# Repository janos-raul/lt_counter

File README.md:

# longitudinal counter 
* [esp32](https://randomnerdtutorials.com/getting-started-with-esp32/) dev board
* [atmega1284p](https://www.aliexpress.com/item/1005007821134063.html?spm=a2g0o.productlist.main.11.9c24lJzhlJzhrd&algo_pvid=f090fad8-6947-47ad-9f22-427393e42094&algo_exp_id=f090fad8-6947-47ad-9f22-427393e42094-5&pdp_npi=4%40dis%21RON%2138.18%2138.18%21%21%2156.89%2156.89%21%402103846917361967912061487e2941%2112000042327493490%21sea%21RO%21187544673%21X&curPageLogUid=a42hYKpOFvhT&utparam-url=scene%3Asearch%7Cquery_from%3A)
* 20x4 [LCD display](https://www.tme.eu/ro/details/rc2004c-ygn-esx/afisaje-lcd-alfanumerice/raystar-optronics/)
* [JDY-41](https://www.aliexpress.com/item/1005003207184013.html?spm=a2g0o.productlist.main.1.15561p5u1p5ukG&algo_pvid=208953bd-97a7-4039-9dab-6f45cec27f1f&algo_exp_id=208953bd-97a7-4039-9dab-6f45cec27f1f-0&pdp_npi=4%40dis%21RON%218.14%218.14%21%21%211.65%211.65%21%402103890917361965765133329ed915%2112000024661701587%21sea%21RO%21187544673%21X&curPageLogUid=vka9Aeq0vKJ6&utparam-url=scene%3Asearch%7Cquery_from%3A) transparent serial port radio module for comunication between the avr and esp32
* [AHT15](https://www.aliexpress.com/item/1005002315840675.html?spm=a2g0o.productlist.main.5.32b8blGTblGTdS&algo_pvid=7e802fce-aae0-4a5e-818c-5492766aa2da&algo_exp_id=7e802fce-aae0-4a5e-818c-5492766aa2da-2&pdp_npi=4%40dis%21RON%219.87%218.69%21%21%212.00%211.76%21%40211b430817361963530388556eb844%2112000043098964036%21sea%21RO%210%21ABX&curPageLogUid=X2Lkd4YSqV8x&utparam-url=scene%3Asearch%7Cquery_from%3A) temperature and humidity sensor
* [SD-card](https://www.aliexpress.com/item/1940258981.html?spm=a2g0o.order_list.order_list_main.9.6ecd1802QFedrz) for logging data and storing html files (also ftp available)
* 1 adc input for diameter measurment with [GS 754B](https://www.leuze.com/en-us/gs-754b-v4-98-s12/50117818)
* 1 counter input (ISR driven)
* 2 adc channels of 0-10v input converting to 0-100%
* 2 open colector outputs
* buzzer for alerts
* 24vcc supply voltage

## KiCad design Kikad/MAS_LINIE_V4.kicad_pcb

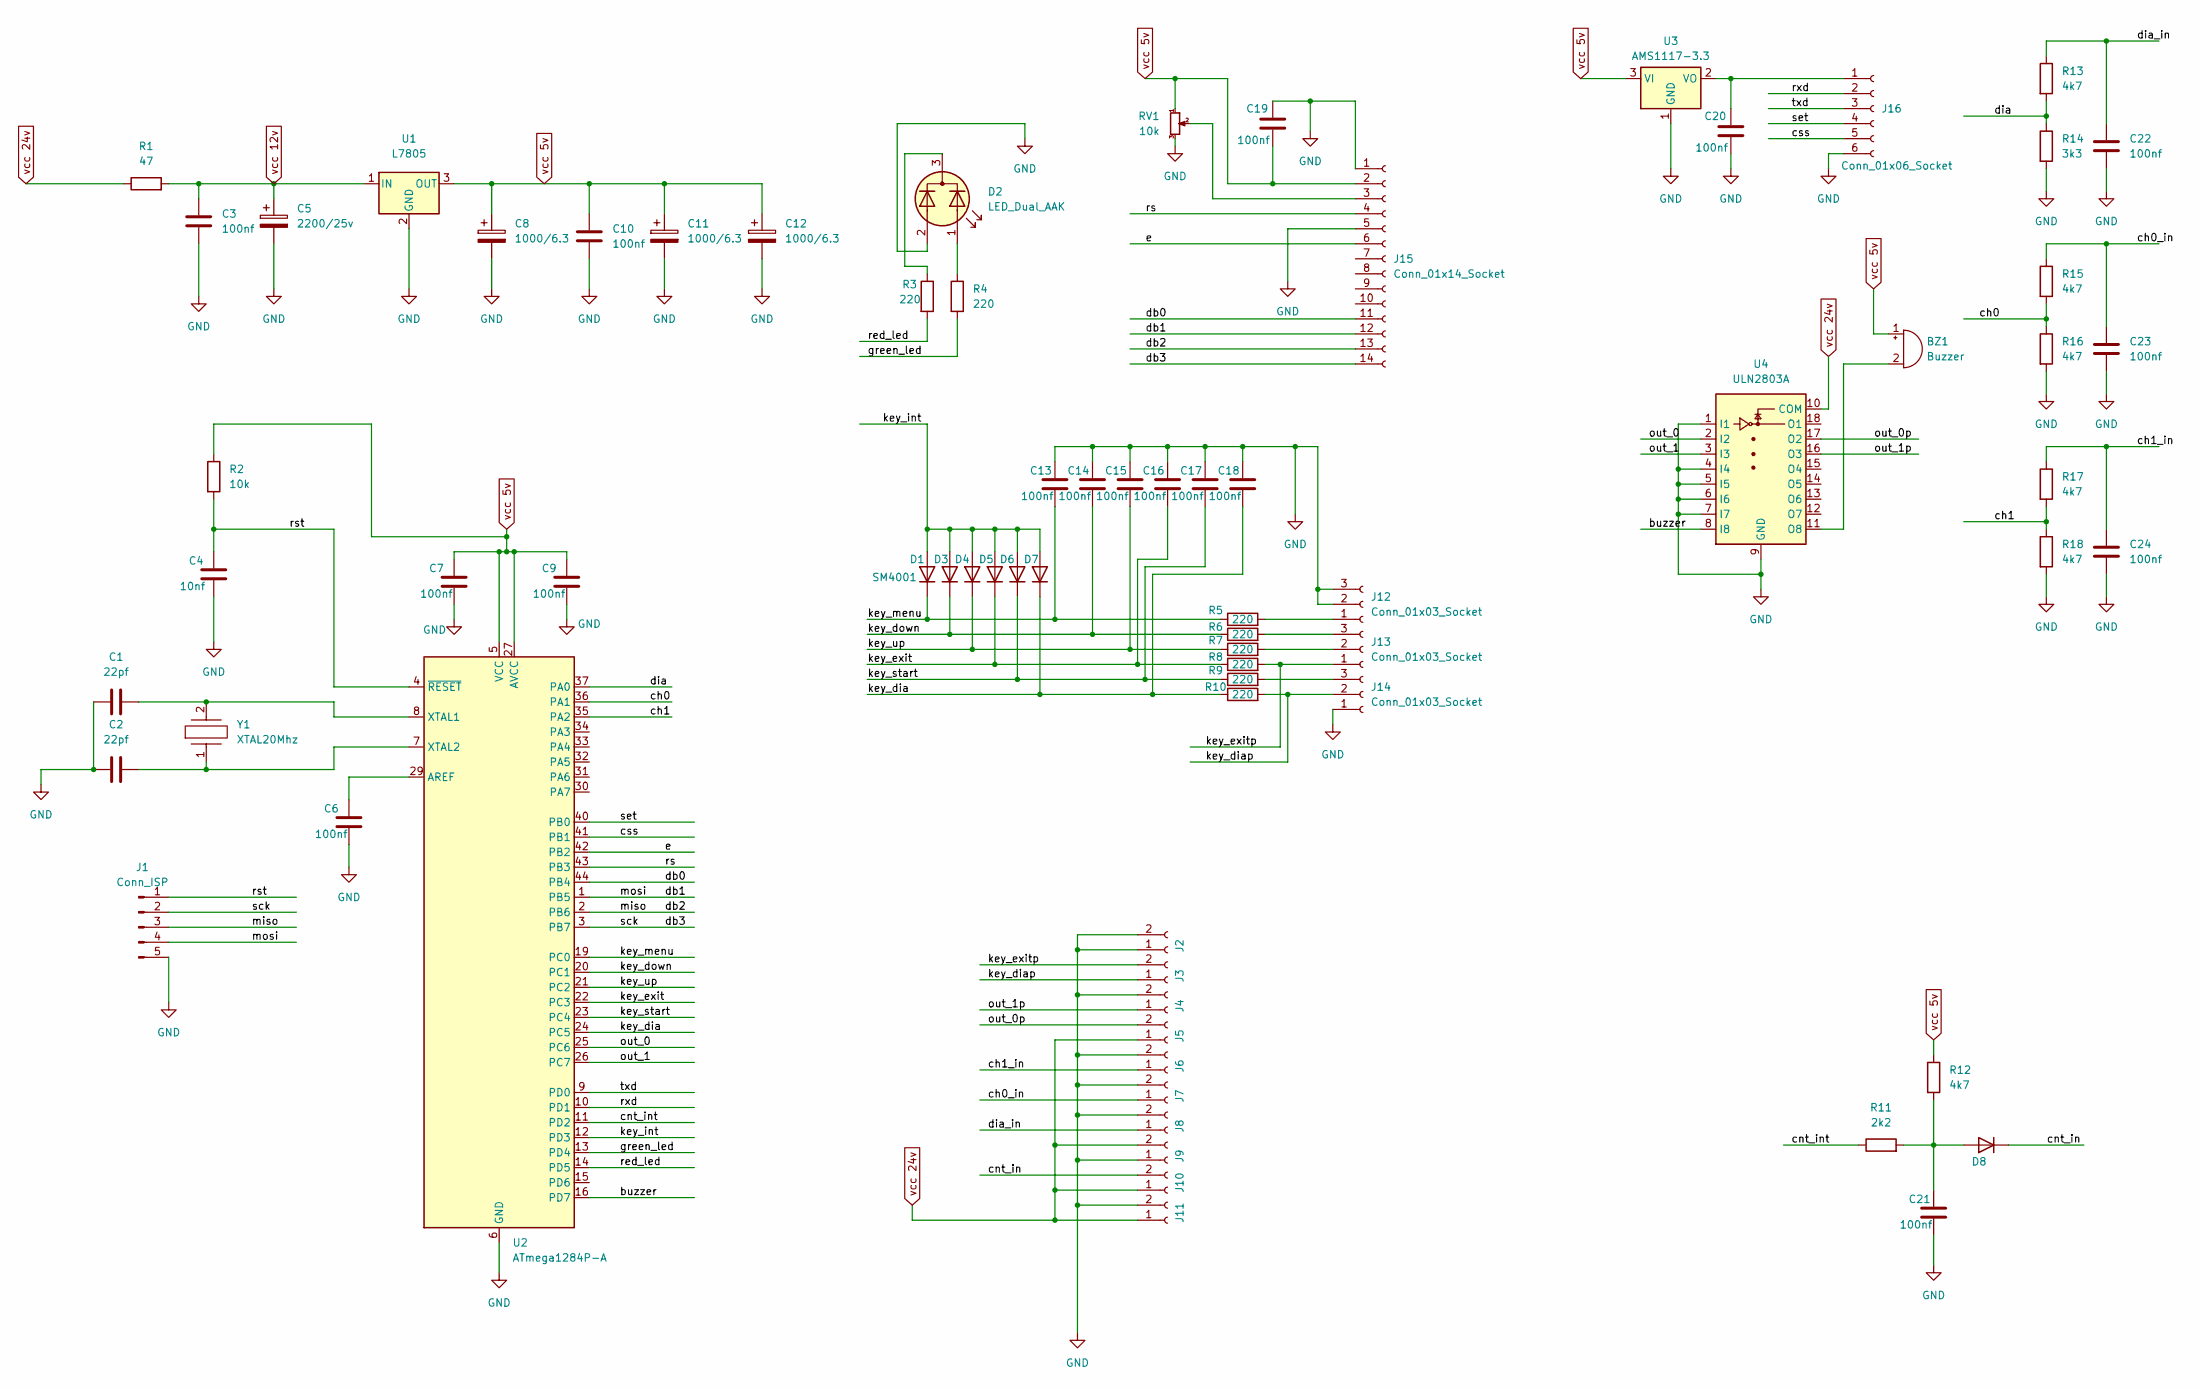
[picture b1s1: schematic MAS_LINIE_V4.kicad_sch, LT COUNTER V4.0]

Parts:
BZ1: Buzzer; Buzzer_12x9.5RM7.6
C1, C2: 22pf; C_1206_3216Metric_Pad1.33x1.80mm_HandSolder
C3, C6, C7, C9, C10, C13, C14, C15, C16, C17, C18, C19, C20, C21, C22, C23, C24: 100nf; C_1206_3216Metric_Pad1.33x1.80mm_HandSolder
C4: 10nf; C_1206_3216Metric_Pad1.33x1.80mm_HandSolder
C5: 2200/25v; CP_Radial_D12.5mm_P5.00mm
C8, C11, C12: 1000/6.3; C_Elec_8x10.2
D1, D3, D4, D5, D6, D7, D8: SM4001; D_2010_5025Metric_Pad1.52x2.65mm_HandSolder
D2: LED_Dual_AAK; DEGSON 3P-3.5pitch
J1: Conn_ISP; PinHeader_1x05_P2.54mm_Vertical
J2, J3, J4, J5, J6, J7, J8, J9, J10, J11: Conn_01x02_Socket; Degson 2p
J12, J13, J14: Conn_01x03_Socket; DEGSON 3P-3.5pitch
J15: Conn_01x14_Socket; PinHeader_1x14_P2.54mm_Vertical
J16: Conn_01x06_Socket; PinHeader_1x06_P2.00mm_Vertical
R1: 47; R_Axial_DIN0411_L9.9mm_D3.6mm_P15.24mm_Horizontal
R2: 10k; R_1206_3216Metric_Pad1.30x1.75mm_HandSolder
R3, R4, R5, R6, R7, R8, R9, R10: 220; R_1206_3216Metric_Pad1.30x1.75mm_HandSolder
R11: 2k2; R_1206_3216Metric_Pad1.30x1.75mm_HandSolder
R12, R13, R15, R16, R17, R18: 4k7; R_1206_3216Metric_Pad1.30x1.75mm_HandSolder
R14: 3k3; R_1206_3216Metric_Pad1.30x1.75mm_HandSolder
RV1: 10k; Potentiometer_ACP_CA6-VSMD_Vertical
U1: L7805; D2PAK-STB35NF10T4
U2: ATmega1284P-A; TQFP-44_10x10mm_P0.8mm
U3: AMS1117-3.3; SOT-223-3_TabPin2
U4: ULN2803A; SOIC-18W_7.5x11.6mm_P1.27mm
Y1: XTAL20Mhz; XTALSMD; Manufacturer_Part_Number LFXTAL003237REEL; Mouser Part Number 449-LFXTAL003237REEL

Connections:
/buzzer: U2.16 (PD7), U4.8 (I8)
/ch0: R15.2, R16.1, U2.36 (PA1)
/ch0_in: C23.1, J7.1, R15.1
/ch1: R17.2, R18.1, U2.35 (PA2)
/ch1_in: C24.1, J6.1, R17.1
/cnt_in: D8.1 (K), J10.2
/cnt_int: R11.1, U2.11 (PD2)
/css: J16.5, U2.41 (PB1)
/db0: J15.11, U2.44 (PB4)
/db1: J1.4, J15.12, U2.1 (PB5)
/db2: J1.3, J15.13, U2.2 (PB6)
/db3: J1.2, J15.14, U2.3 (PB7)
/dia: R13.2, R14.1, U2.37 (PA0)
/dia_in: C22.1, J8.1, R13.1
/e: J15.6, U2.42 (PB2)
/green_led: R4.2, U2.13 (PD4)
/key_dia: C18.2, D7.1 (K), R10.1, U2.24 (PC5)
/key_diap: J3.1, J14.2, R10.2
/key_down: C14.2, D3.1 (K), R6.1, U2.20 (PC1)
/key_exit: C16.2, D5.1 (K), R8.1, U2.22 (PC3)
/key_exitp: J3.2, J13.1, R8.2
/key_int: D1.2 (A), D3.2 (A), D4.2 (A), D5.2 (A), D6.2 (A), D7.2 (A), U2.12 (PD3)
/key_menu: C13.2, D1.1 (K), R5.1, U2.19 (PC0)
/key_start: C17.2, D6.1 (K), R9.1, U2.23 (PC4)
/key_up: C15.2, D4.1 (K), R7.1, U2.21 (PC2)
/out_0: U2.25 (PC6), U4.2 (I2)
/out_0p: J5.2, U4.17 (O2)
/out_1: U2.26 (PC7), U4.3 (I3)
/out_1p: J4.1, U4.16 (O3)
/red_led: R3.2, U2.14 (PD5)
/rs: J15.4, U2.43 (PB3)
/rst: C4.1, J1.1, R2.2, U2.4 (~RESET)
/rxd: J16.2, U2.10 (PD1)
/set: J16.4, U2.40 (PB0)
/txd: J16.3, U2.9 (PD0)
GND: C1.1, C2.1, C3.2, C4.2, C5.2, C6.2, C7.2, C8.2, C9.2, C10.2, C11.2, C12.2, C13.1, C14.1, C15.1, C16.1, C17.1, C18.1, C19.1, C20.2, C21.2, C22.2, C23.2, C24.2, D2.2 (A2), J1.5, J2.1, J2.2, J4.2, J6.2, J7.2, J8.2, J9.1, J11.2, J12.2, J12.3, J14.1, J15.1, J15.5, J16.6, R14.2, R16.2, R18.2, RV1.3, U1.2 (GND), U2.6 (GND), U2.18 (GND), U2.28 (GND), U2.39 (GND), U3.1 (GND), U4.1 (I1), U4.4 (I4), U4.5 (I5), U4.6 (I6), U4.7 (I7), U4.9 (GND); also elsewhere on the board
unnamed: BZ1.2 (-), U4.11 (O8)
unnamed 37: D2.1 (A1), R4.1; also elsewhere on the board
unnamed 38: D2.3 (K), R3.1; also elsewhere on the board
unnamed: C21.1, D8.2 (A), R11.2, R12.2
unnamed: J12.1, R5.2
unnamed: J13.2, R7.2
unnamed: J13.3, R6.2
unnamed: J14.3, R9.2
unnamed: J15.3, RV1.2
unnamed: C20.1, J16.1, U3.2 (VO)
unnamed: C6.1, U2.29 (AREF)
unnamed: C1.2, U2.8 (XTAL1), Y1.2
unnamed: C2.2, U2.7 (XTAL2), Y1.1
vcc 5v: BZ1.1 (+), C7.1, C8.1, C9.1, C10.1, C11.1, C12.1, C19.2, J15.2, R2.1, R12.1, RV1.1, U1.3 (OUT), U2.5 (VCC), U2.17 (VCC), U2.27 (AVCC), U2.38 (VCC), U3.3 (VI)
vcc 12v: C3.1, C5.1, R1.2, U1.1 (IN)
vcc 24v: J5.1, J9.2, J10.1, J11.1, R1.1, U4.10 (COM)

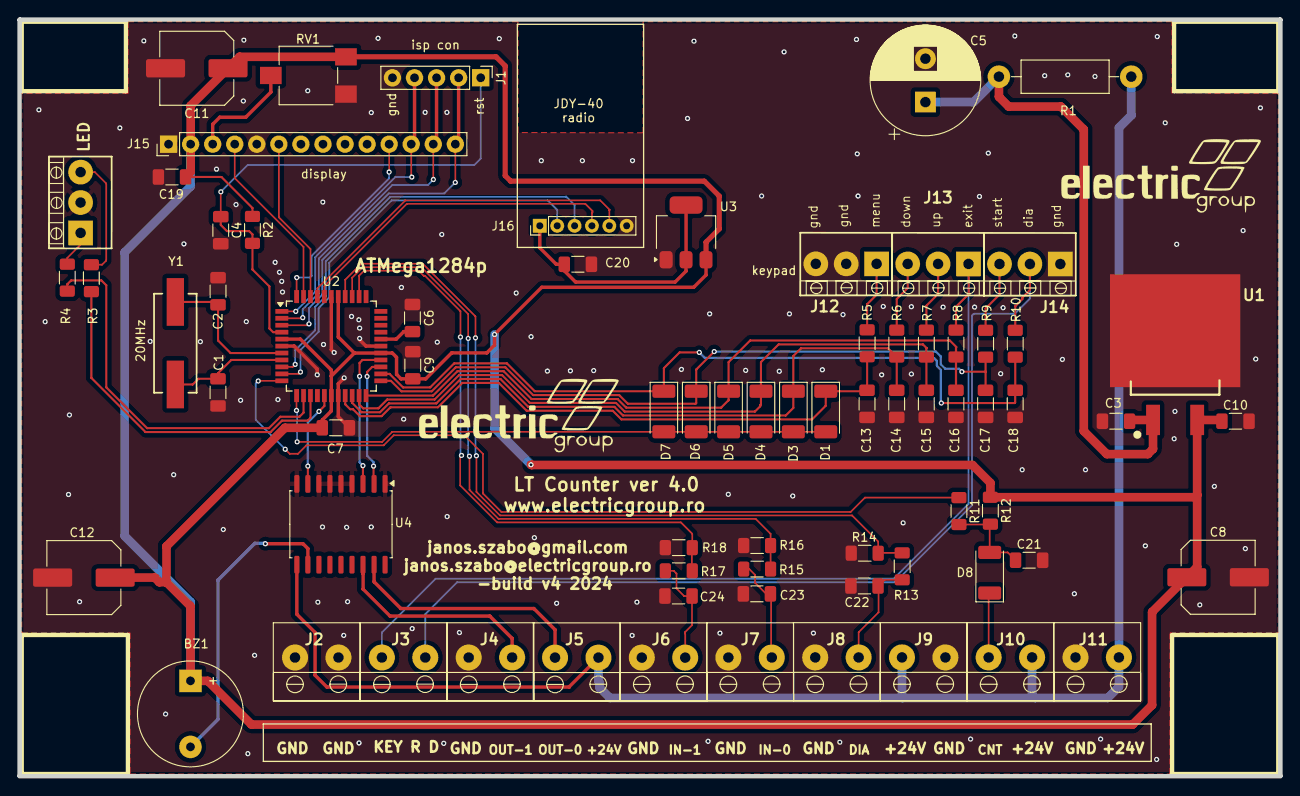
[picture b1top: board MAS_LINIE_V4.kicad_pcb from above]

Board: 2 copper layers, 145.2 x 87.1 mm, 73 parts (0 on the bottom side), 52 nets.

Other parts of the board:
LED: LED_Dual_AAK; DEGSON 3P-3.5pitch

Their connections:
GND: LED.2 (A2); also elsewhere on the board
unnamed 37: LED.1 (A1); also elsewhere on the board
unnamed 38: LED.3 (K); also elsewhere on the board

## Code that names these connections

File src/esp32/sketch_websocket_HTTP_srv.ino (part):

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#include <AHTxx.h>

#define PIN_SPI_CS 5  // The ESP32 pin GPIO5
#define GREEN_LED_PIN 2
#define RED_LED_PIN 15
#define TXD2 16
#define RXD2 17
#define JDY_CSS 0
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      srvclients++;
      if (srvclients >= maxClients) {
        client->text("redirect");
        digitalWrite(RED_LED_PIN, HIGH);
        // Serial.printf("WebSocket client #%u rejected from %s\n", client->id(), client->remoteIP().toString().c_str());
      }  //else {
         // Serial.printf("WebSocket client #%u connected from %s\n", client->id(), client->remoteIP().toString().c_str());
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      // Serial.print("ESP32 Web Server Hostname: ");
      // Serial.println(WiFi.getHostname());
      ip = WiFi.localIP().toString();
      digitalWrite(RED_LED_PIN, LOW);
      return;
    } else {
      // Serial.println("Failed to connect");
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
void checkWiFiConnection() {
  if (WiFi.status() != WL_CONNECTED) {
    digitalWrite(RED_LED_PIN, HIGH);
    digitalWrite(GREEN_LED_PIN, LOW);
    // Serial.println("WiFi connection lost. Reconnecting...");
    connectToWiFi();
  }
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}

void setup() {
  pinMode(GREEN_LED_PIN, OUTPUT);  // set ESP32 pin to output mode
  pinMode(RED_LED_PIN, OUTPUT);    // set ESP32 pin to output mode
  pinMode(JDY_CSS, OUTPUT);        // set ESP32 pin to output mode
  pinMode(JDY_SET, OUTPUT);        // set ESP32 pin to output mode
  digitalWrite(JDY_CSS, LOW);
  digitalWrite(JDY_SET, HIGH);
  digitalWrite(RED_LED_PIN, HIGH);
  //delay(5000);
  Serial.begin(115200);
  // Serial.flush();
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      aht_flag = false;
      temp = "Sensor malfunction!";
      hum = "Sensor malfunction!";
      digitalWrite(RED_LED_PIN, HIGH);
      return;
    }

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  // init MicroSD Card
  if (!SD.begin(PIN_SPI_CS)) {
    // Serial.println("SD Card initialization failed");
    digitalWrite(RED_LED_PIN, HIGH);
    return;
  }
  //Serial.println("SD Card initialized!");
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      // Serial.println("Created /log directory");
    } else {
      //  Serial.println("Failed to create /log directory");
      digitalWrite(RED_LED_PIN, HIGH);
    }
  }
}
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  if (((currentMillis - lastTime2) >= timerDelay2) && (srvclients > 0)) {
    lastTime2 = currentMillis;
    led_state = !led_state;
    digitalWrite(GREEN_LED_PIN, led_state);
  }
  if (((currentMillis - lastTime3) >= timerDelay3) && (srvclients == 0) && (WiFi.status() == WL_CONNECTED)) {
    lastTime3 = currentMillis;
    led_state = !led_state;
    digitalWrite(GREEN_LED_PIN, led_state);
    digitalWrite(RED_LED_PIN, LOW);
  }
  /*
  // Handle mySerial input
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      // Serial.println("Radio RX: " + radiomessage);
      extractSubstrings(radiomessage, parts, maxParts);
      processRadioMessage(parts);
      digitalWrite(RED_LED_PIN, LOW);
    } else {
      digitalWrite(RED_LED_PIN, HIGH);
      Serial.println("Radio Rx message discarded.");
      sendData("RX error-----------------");
    }
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    processRadioMessage(parts);

    // Turn off the RED LED
    digitalWrite(RED_LED_PIN, LOW);
  } else {
    // Turn on the RED LED to indicate an error
    digitalWrite(RED_LED_PIN, HIGH);
    //Serial.println("Radio RX: message discarded.");
    //mySerial.print("Radio RX: " + radiomessage);
    //mySerial.println("->>> message discarded.");
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
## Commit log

2025-01-14 Update interupts.inc
    updated green led off cycle.
